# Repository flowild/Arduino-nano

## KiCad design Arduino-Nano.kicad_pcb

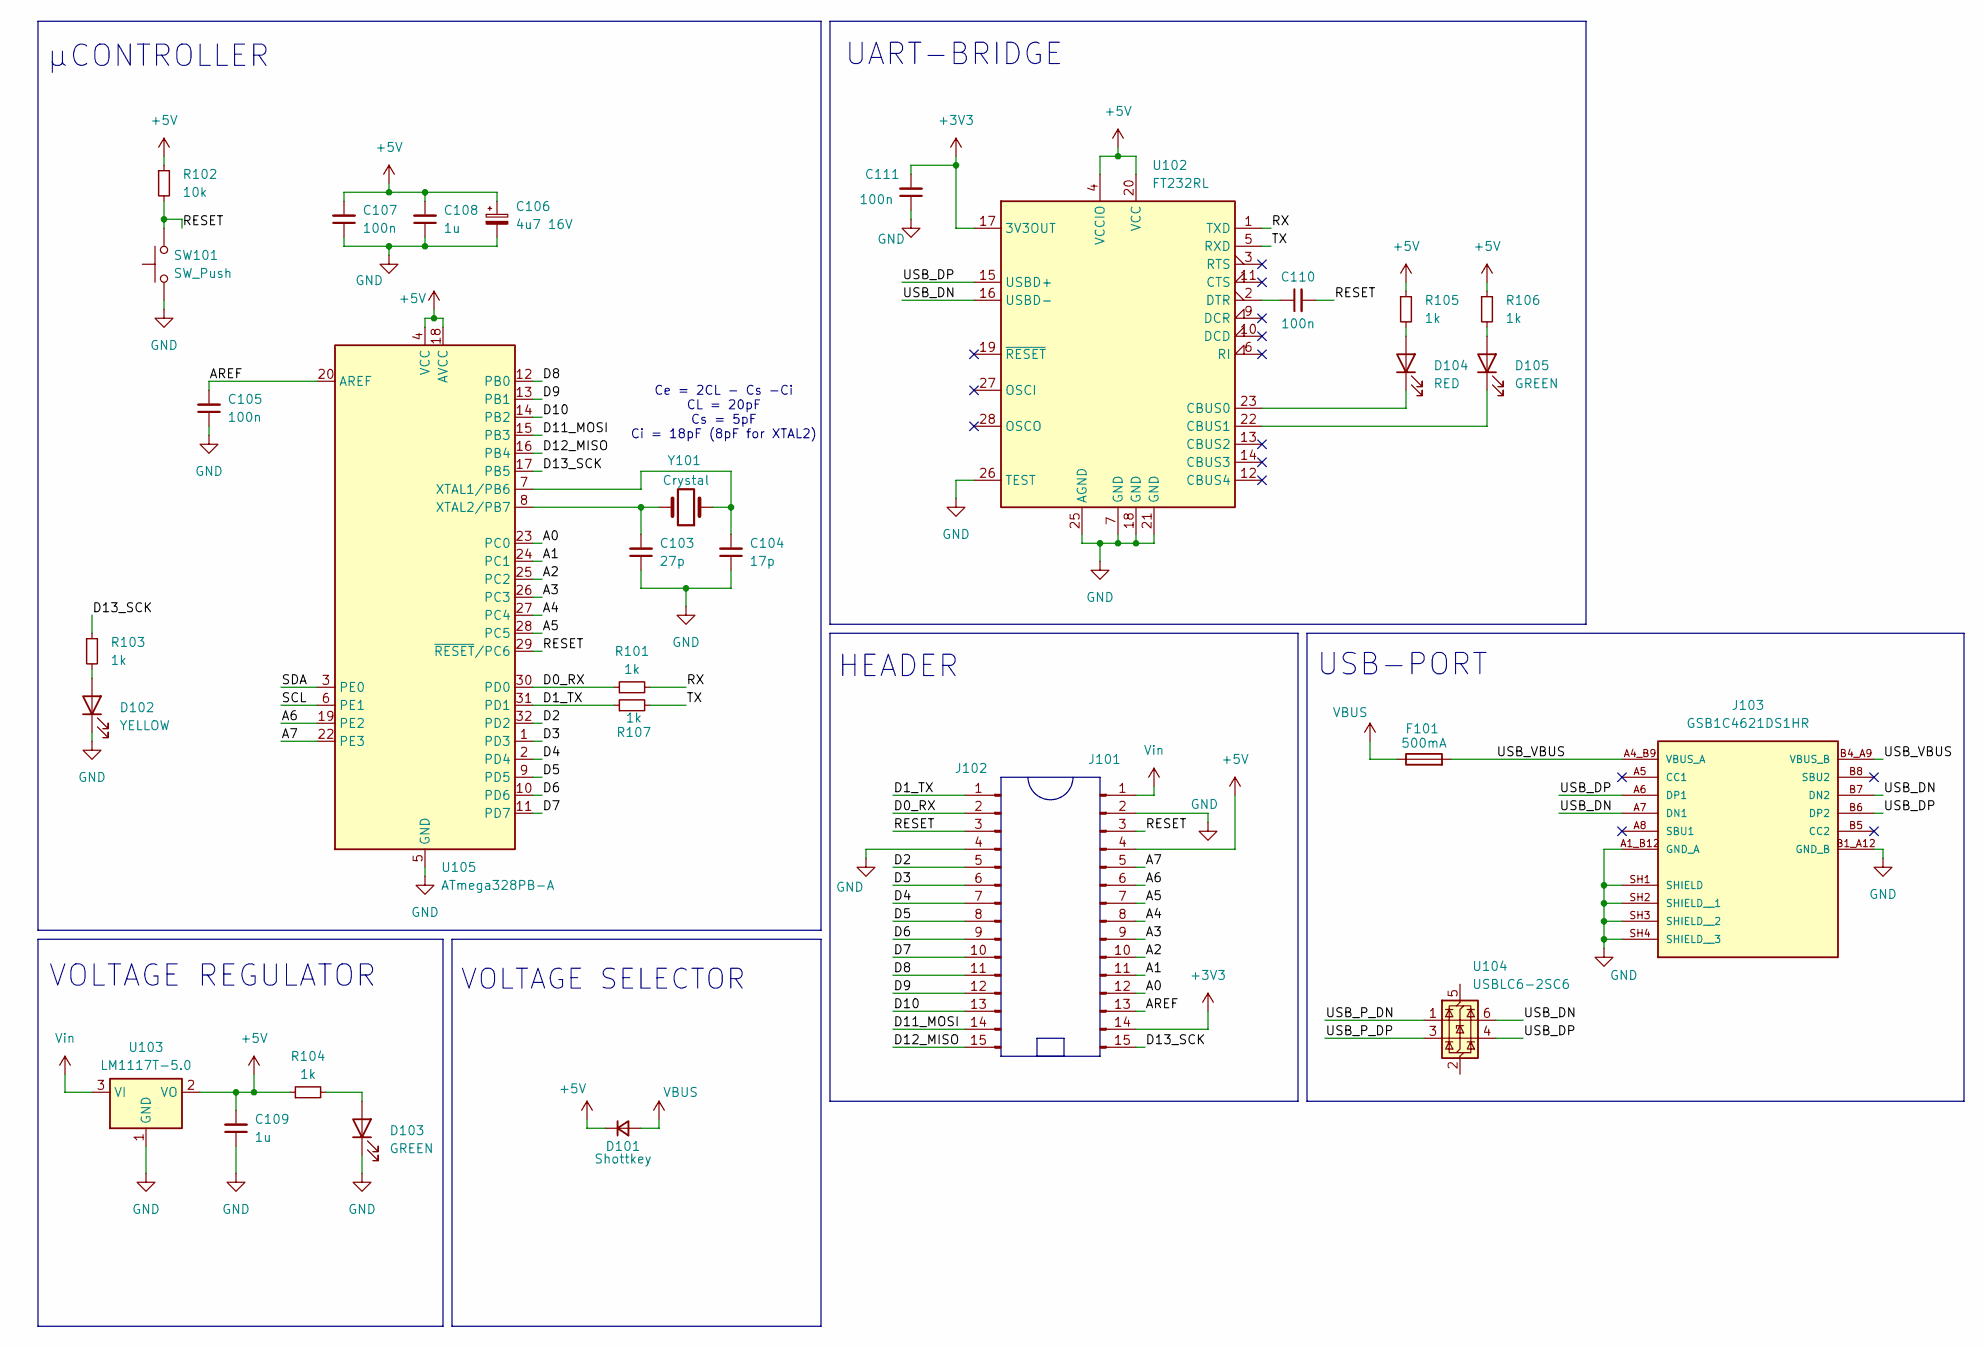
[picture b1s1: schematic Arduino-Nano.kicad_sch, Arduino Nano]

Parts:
C103: 27p; C_0402_1005Metric; MPN GRM1555C1H270JA01D
C104: 17p; C_0402_1005Metric; MPN GJM1555C1H170FB01D
C105, C107, C110, C111: 100n; C_0402_1005Metric; MPN GRM155R71C103KA01D
C106: 4u7 16V; C_0603_1608Metric; MPN GRT188R61E475ME13D
C108, C109: 1u; C_0402_1005Metric; MPN GRM155R61E105MA12D
D101: Shottkey; D_SOD-123; MPN MBR130LSFT1G
D102: YELLOW; LED_0402_1005Metric_B2841UY--20; MPN B2841UY--20D000414U1930
D103, D105: GREEN; LED_0402_1005Metric_B2841UY--20; MPN B2841NG--05D000514U1930
D104: RED; LED_0402_1005Metric_B2841UY--20; MPN B2841USD-20D001014U1930
F101: 500mA; Fuse_0805_2012Metric; MPN SMD0805B050TF
J101, J102: Conn_01x15_Pin; PinHeader_1x15_P2.54mm_Vertical; MPN PH1-15-UA
J103: GSB1C4621DS1HR; AMPHENOL_GSB1C4621DS1HR; MPN GSB1C4621DS1HR
R101, R103, R104, R105, R106, R107: 1k; R_0402_1005Metric; MPN RC0402JR-071KL
R102: 10k; R_0402_1005Metric; MPN RC0402JR-0710KL
SW101: SW_Push
U102: FT232RL; SSOP-28_5.3x10.2mm_P0.65mm
U103: LM1117T-5.0; TO-220-3_Horizontal_TabDown
U104: USBLC6-2SC6; SOT-23-6
U105: ATmega328PB-A; QFN-32-1EP_5x5mm_P0.5mm_EP3.45x3.45mm; MPN ATMEGA328PB-MUR
Y101: Crystal; Crystal_SMD_3225-4Pin_3.2x2.5mm; MPN RH100-16.000-10-1010-EXT-TR

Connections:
+3V3: C111.2, J101.14, U102.17 (3V3OUT)
+5V: C106.1, C107.2, C108.2, C109.2, D101.1 (K), J101.4, R102.1, R104.1, R105.1, R106.1, U102.4 (VCCIO), U102.20 (VCC), U103.2 (VO), U105.4 (VCC), U105.18 (AVCC)
/A0: J101.12, U105.23 (PC0)
/A1: J101.11, U105.24 (PC1)
/A2: J101.10, U105.25 (PC2)
/A3: J101.9, U105.26 (PC3)
/A4: J101.8, U105.27 (PC4)
/A5: J101.7, U105.28 (PC5)
/A6: J101.6, U105.19 (PE2)
/A7: J101.5, U105.22 (PE3)
/AREF: C105.2, J101.13, U105.20 (AREF)
/D0_RX: J102.2, R101.1, U105.30 (PD0)
/D1_TX: J102.1, R107.1, U105.31 (PD1)
/D2: J102.5, U105.32 (PD2)
/D3: J102.6, U105.1 (PD3)
/D4: J102.7, U105.2 (PD4)
/D5: J102.8, U105.9 (PD5)
/D6: J102.9, U105.10 (PD6)
/D7: J102.10, U105.11 (PD7)
/D8: J102.11, U105.12 (PB0)
/D9: J102.12, U105.13 (PB1)
/D10: J102.13, U105.14 (PB2)
/D11_MOSI: J102.14, U105.15 (PB3)
/D12_MISO: J102.15, U105.16 (PB4)
/D13_SCK: J101.15, R103.1, U105.17 (PB5)
/RESET: C110.2, J101.3, J102.3, R102.2, SW101.2, U105.29 (~RESET/PC6)
/RX: R101.2, U102.1 (TXD)
/SCL: U105.6 (PE1)
/SDA: U105.3 (PE0)
/TX: R107.2, U102.5 (RXD)
/USB_DN: J103.A7 (DN1), J103.B7 (DN2), U102.16 (USBD-), U104.6 (I/O1)
/USB_DP: J103.A6 (DP1), J103.B6 (DP2), U102.15 (USBD+), U104.4 (I/O2)
/USB_P_DN: U104.1 (I/O1)
/USB_P_DP: U104.3 (I/O2)
/USB_VBUS: F101.2, J103.A4_B9 (VBUS_A), J103.B4_A9 (VBUS_B)
GND: C103.1, C104.1, C105.1, C106.2, C107.1, C108.1, C109.1, C111.1, D102.1 (K), D103.1 (K), J101.2, J102.4, J103.A1_B12 (GND_A), J103.B1_A12 (GND_B), J103.SH1 (SHIELD), J103.SH2 (SHIELD__1), J103.SH3 (SHIELD__2), J103.SH4 (SHIELD__3), SW101.1, U102.7 (GND), U102.18 (GND), U102.21 (GND), U102.25 (AGND), U102.26 (TEST), U103.1 (GND), U105.5 (GND), U105.21 (GND)
unnamed: D102.2 (A), R103.2
unnamed: D103.2 (A), R104.2
unnamed: D104.2 (A), R105.2
unnamed: D104.1 (K), U102.23 (CBUS0)
unnamed: D105.2 (A), R106.2
unnamed: D105.1 (K), U102.22 (CBUS1)
unnamed: C110.1, U102.2 (DTR)
unnamed: C104.2, U105.7 (XTAL1/PB6), Y101.1
unnamed: C103.2, U105.8 (XTAL2/PB7), Y101.2
VBUS: D101.2 (A), F101.1
Vin: J101.1, U103.3 (VI)

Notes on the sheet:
VOLTAGE REGULATOR
UART-BRIDGE
VOLTAGE SELECTOR
Ce = 2CL - Cs -Ci CL = 20pF Cs = 5pF Ci = 18pF (8pF for XTAL2)
USB-PORT
µCONTROLLER
HEADER

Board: 4 copper layers, 29 parts (0 on the bottom side), 42 nets, no tracks yet.
